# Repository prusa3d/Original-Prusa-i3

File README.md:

# Original Prusa i3 MK3S

Original Prusa i3 MK3S is a 3D printer project maintained by PRUSA RESEARCH.
Originates in [RepRap](https://reprap.org) project made possible by Dr. Adrian Bowyer and contributors.

This repository contains SCAD files and STLs of the printed parts.

**Links**

 * Prusa Research website : http://prusa3d.com
 * Product page: https://shop.prusa3d.com/en/3d-printers/180-original-prusa-i3-mk3-kit.html
 * Build manual: https://manual.prusa3d.com/c/Original_Prusa_i3_MK3S_kit_assembly
 * Firmware : https://github.com/prusa3d/Prusa-Firmware
 * MK52 heatbed : https://github.com/prusa3d/Heatbed_MK52_magnetic
 * MK3 Power panic : https://github.com/prusa3d/MK3_Power_Panic
 * MK3S IR senzor : https://github.com/prusa3d/MKxS-IR-sensor

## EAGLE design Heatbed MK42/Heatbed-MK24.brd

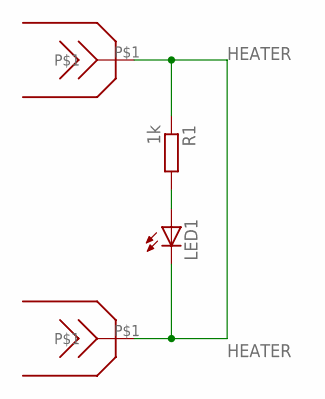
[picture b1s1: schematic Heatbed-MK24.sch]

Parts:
LED1: LEDCHIPLED_0805; CHIPLED_0805
R1: 1k; M0805
U$1, U$2: FASTONSMD

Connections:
HEATER: LED1.C, R1.1, U$1.P$1, U$2.P$1
unnamed: LED1.A, R1.2

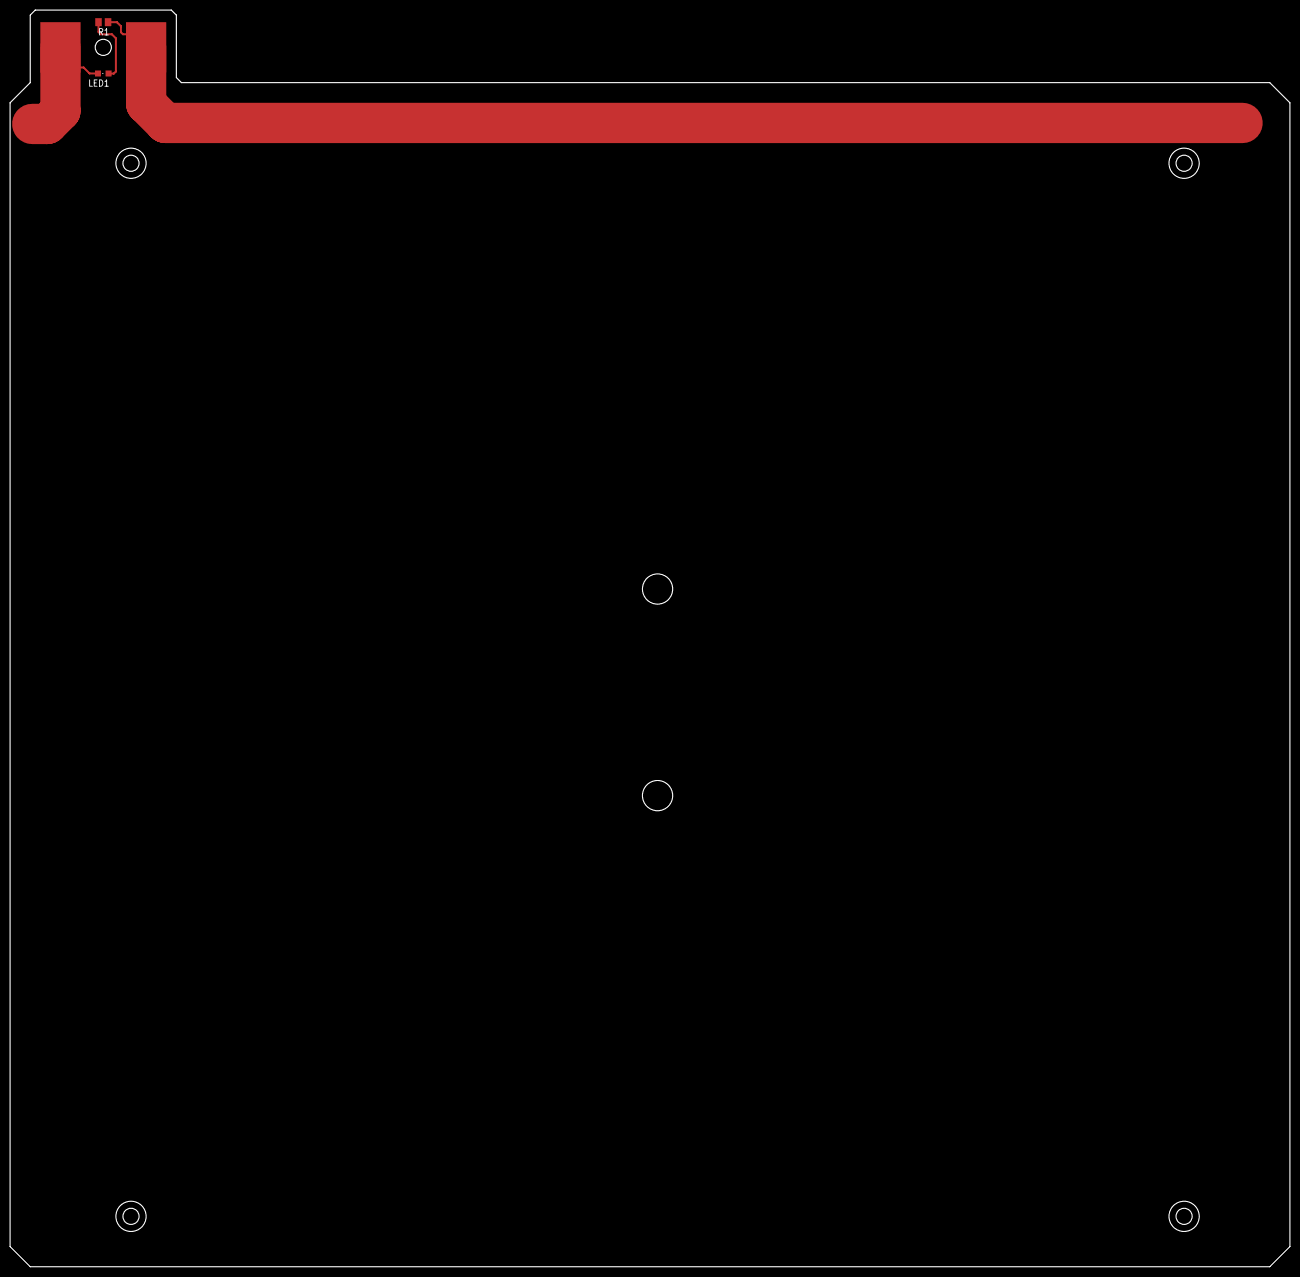
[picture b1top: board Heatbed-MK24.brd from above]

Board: 6 copper layers, 254.0 x 249.4 mm, 4 parts (0 on the bottom side), 2 nets.

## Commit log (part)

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2017-12-22 Fixed Frame Thickness
2017-12-22 Parasolid Binary (Ver 26.0) - Fixed Frame
2018-01-06 Narrowing Belt Gap R
    ### Description
    The belt gap R is a little too wide allowing the belt to slip off of the carriage part.
    ### Proposed Changes
    - change the cube on the bottom of the belt gap increasing the Y from 7.5 to 8 to make the belt gap more narrow (1.95mm gap)
2018-01-06 Replacing STL
    - updating the STL with the newly updated belt gap R (1.95mm)
2018-01-10 Heatbed cable cover with screw clip
2018-01-14 Converted new heatbed cover to STEP
2018-01-14 Added new Heatbed Cover
2018-01-22 Rotated to proper print position
2018-01-25 y-rod-holder added
2018-02-02 Adjusted X-IDLER pulley screw holes to better match m3 screw size
2018-02-04 Adjust x-end-idler pulley screw hole to exactly match M3 screw That solves problem with pulley being not alignred correctly as mentioned in #50
2018-02-11 removed, replaced by y-rod-holder
2018-02-11 screws and nuts tolerances
2018-02-11 tolerances
2018-02-11 screws & nuts tolerances , rotated to proper print position
2018-02-11 extruder screw clearance, tolerances
2018-02-11 SD card window size & supports
2018-02-11 motor opening, tolerances
2018-02-11 thin wall cut, tolerances
2018-02-11 belt tensioner, pulley screw fix, trapeziod nut reinforcement, tolerances
2018-02-11 Belt holder change, tolerances
2018-02-11 Tolerances, motor opening & clearance
2018-02-13 Fix #50 - x axis pulley screw missaligment due to holes being to big on one side
2018-02-14 Fix clearance for M3 screw and head of belt pulley to solve wobbling
2018-02-14 Converted the new R2 files to STEP
2018-02-15 Cosmetic post c7888d9630747e242883316f5b17df5d3c70fee1
2018-02-17 Fixed mirrored part
2018-02-17 Fixed Missing Hole
2018-02-18 Create SolidWorks (R2)
2018-02-18 Create kjlj
2018-02-18 New SolidWorks Assembly with R2 parts
2018-02-18 New Assembly with R2 parts
2018-02-21 Fixed Holes; converted by user jltx
2018-02-21 fixed x-end motor
2018-02-21 fixed x-end motor part
2018-02-22 Heatbed cable cover added
2018-03-01 Readme updated
2018-03-03 Minor Patch to fix bearing diameter
    * corrected spelling of length
    * updated `vertical_bearing_holes` to use bearing_diameter on line 70
2018-03-05 X-carriage belt holder
2018-03-21 initial version
2018-04-05 MK2S to MK3 upgrade - Parts list
2018-04-10 Added bltouch mount to MK3 Extruder
2018-04-10 Removed pinda from scad in bltouch version
2018-04-17 Screw mounted cables version
2018-04-17 PSU cover added
2018-04-26 Older type of heatbed cover without screw holes
2018-05-03 Filename changed + content updated
2018-05-30 TZB-CenteredYAxisHoming
    I have redesigned the Y-Motor-holder to incorporate a hard stop for the hotbed belt mount so the load is centered to the motor and removes the random skew introduced.
2018-05-30 TZB-CenteredYAxisHoming-STL
    I have redesigned the Y-Motor-holder to incorporate a hard stop for the hotbed belt mount so the load is centered to the motor and removes the random skew introduced. STL SCAD Export.
2018-06-07 Fixed text "HOT!2 protruding inside
    To get a better airflow, it is necessary to fix the buggy positioning of the "HOT!2", so that it does not reach INSIDE the nozzle fan duct
2018-06-07 Adjust fan cut to real fan size
    This makes sure that less air leaves the fan duct in the front
2018-06-08 Fixed a typo introduced earlier
2018-07-08 New STEP files added
2018-07-08 New PSU and other small changes
2018-07-17 Heatbreak and print cooling update
    Extruder body and cover : Improved cooling of the heatbreak by redesigning intake / outtake of cooling air with additional air feed opening. Improved PTFE tube holder for better flex materials handli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
2018-08-01 Heatbreak and print cooling update
2018-08-01 Angled fan version
2018-08-01 Heatbreak and print cooling update
    Heatbreak and print cooling update, removed second unused screw, cables clearance
2018-08-02 Create jklj
2018-08-02 Added R3 SolidWorks Version
2018-08-02 Added R3 STEP files
2018-08-13 Information about parts updated
    See P3-93 in YouTrack
2018-09-02 Create hjk
2018-09-27 general changes
2018-09-27 new cable clips, raspberry doors, cable management
    - new extruder and heatbed cable holders, clips
    - ziptie cable management added
    - new popup doors for raspberry pi (raspberry pi cover available)
2018-09-27 resize to fit with Einsy_base
2018-09-27 extruder cable clip for new Einsy_base
2018-09-27 heatbed cable clip for new Einsy_base
2018-09-27 heatbed cable clip for new Einsy_base (8mm sleeve)
2018-09-27 nut holders edited, sleeve size changed to 6mm
2018-09-27 better nylon holder, nut inserts edited
2018-09-27 improved nut traps, wall thickness expanded
2018-09-27 improved nut traps
2018-09-27 selective infill improved
2018-09-27 tolerances changes
2018-09-27 wall thickness chages
2018-09-27 raspberry cover for einsy base, iitial versio
2018-10-01 new cable clips, raspberry doors, cable management
2018-10-01 Older type of heatbed cover without screw holes (8mm sleeve)
2018-10-01 Screw mounted cables version (8mm sleeve)
2018-10-01 Older type of heatbed cover without screw holes(8mm sleeve)
2018-10-01 nut holders edited (8mm sleeve)
2018-10-02 Change file content (see CONTENT-225 issue)
2018-10-09 Thicker wall for X-idler bolt
2018-10-09 Restored strengthening for X-idler
2018-10-10 Updated x-end-idler STL
2018-10-11 Whitespace, indenting cleanup
2018-10-11 Quick script to render all parts
2018-10-12 Part rotated top proper print position
2018-10-14 Cleanup of whitespace, codestyle, indentation
2018-10-23 Updated with MMU2 part info
2018-10-24 Added editorconfig to promote code consistency
2019-01-14 plug aligner added
    plug aligner added
2019-02-12 MK3S initial
2019-02-19 tweak link to manual
2019-02-19 Wall thickness adjusted for better printing
2019-02-27 MK2.5S initial
2019-03-01 Filament buffer parts added
    Filament buffer parts added
2019-03-22 psu-cover-DELTA added
2019-04-02 Buffer hook added ( uni )
    Universal version compatible with MK2.5 and MK3 printers
2019-04-02 Buffer hook added ( universal )
    Universal version compatible with MK2.5 and MK3 printers
2019-04-02 1. Added new STL of the Einsy-base as a variant without the fixed raspberry cover, instead you could print the raspberry_cover.stl for the clip-in cover.
    2. In all .scad files that have a revision stamp in it a variable "rev" in the
    beginning of the code was introduced and used in the 'text' functions
    instad of using strings directly.
    Exapmle:
    rev = "R3";
    text(rev, font = "helvetica:style=Bold", size=6, center=true);
2019-04-03 Part version identifier change
    Strictly version mark change to identify source of the parts
2019-06-10 Heatbed cable cover using opposite screw direction
2019-06-10 Part rotated to proper print position
2019-07-11 Added missing part
2019-07-25 Reinforced fin and PINDA holder
    Reinforced fin at the bottom of the heatsink and PINDA holder to avoid melting when printing with higher temperatures.
2019-07-26 Left / Right marking added
2019-11-06 Create Einsy-base-usb
    Einsy base with removed Raspberry Pi cover and extra hole for connecting microUSB cable to connect camera. See:
    https://www.thingiverse.com/thing:3959958
2020-03-03 Improved blade holder
    Improved blade holder, adjusted geometry for better filament cut
2020-04-19 Nut holes had different sizes
2020-07-24 rebuilt optimized SCAD for rpi-zero-frame.scad, regenerate rpi-zero-frame.stl
2020-12-07 MK3S+ upgrade
    MK3S+ upgrade
2020-12-26 Added cable breakage preventing protusions. Hours of wasted life will be saved
2020-12-26 Exported stl of heatbed-cable-cover-clip
2020-12-26 Changing line end characters to match original file
2021-01-15 Resolve OpenSCAD "WARNING: Cylinder parameters ambiguous"
2021-01-23 Update README.md
    fix typo
2021-03-08 x-end-idler.scad: fix warning
2021-03-28 Update LCD-cover-ORIGINAL-MK3.scad
    removed "center=true" from text(), throws OpenSCAD error. There is a way to align text using valign and halign if desired.
    changed r to r1 on line 155, OpenSCAD throwing error indicating cylinder parameters are ambiguous.
2021-04-19 scad for rpi-zero-frame
2021-05-01 Updated R3 extruder idler plug with no IR reflection
2021-06-08 R7 - x axis bearings / lcd window
    x-carriage linear bearings holder update
    LCD window frame adjustment
2021-12-09 Space for screws is slightly misplaced
    Space for extruder screws in X-Carriage is off by .5mm. This is mostly cosmetic problem, but fix is trivial.
2022-03-14 RaspberryPi Zero 2 fix
2022-09-21 Update
    Update to the description regarding RepRap project.
2022-10-21 Update x-carriage.scad
    The filament hole doe snot completely pass trhourgh the surface. (changed the trabslate from 0 to -5)
2022-11-09 Increase the R6 version number
2022-11-14 Missing version info added
2024-03-10 correct some warnings in the OpenSCAD code
    The following issues are corrected by this change:
    1. The text module does not have a "center" parameter, therefore
    there is no point in specifying it.
    2. In some places for cylinders "r" and "r2" where specified instead
    of "r1" and "r2".
    3. In some places the start value was larger than the end value in
